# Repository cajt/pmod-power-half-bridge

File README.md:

# pmod-power-half-bridge
This is a power electronics building block for use with an FPGA board that supports PMOD Interfaces. It contains a GAN based half-bridge, an optional LC low-pass output filter, and two ADCs for current and voltage feedback.

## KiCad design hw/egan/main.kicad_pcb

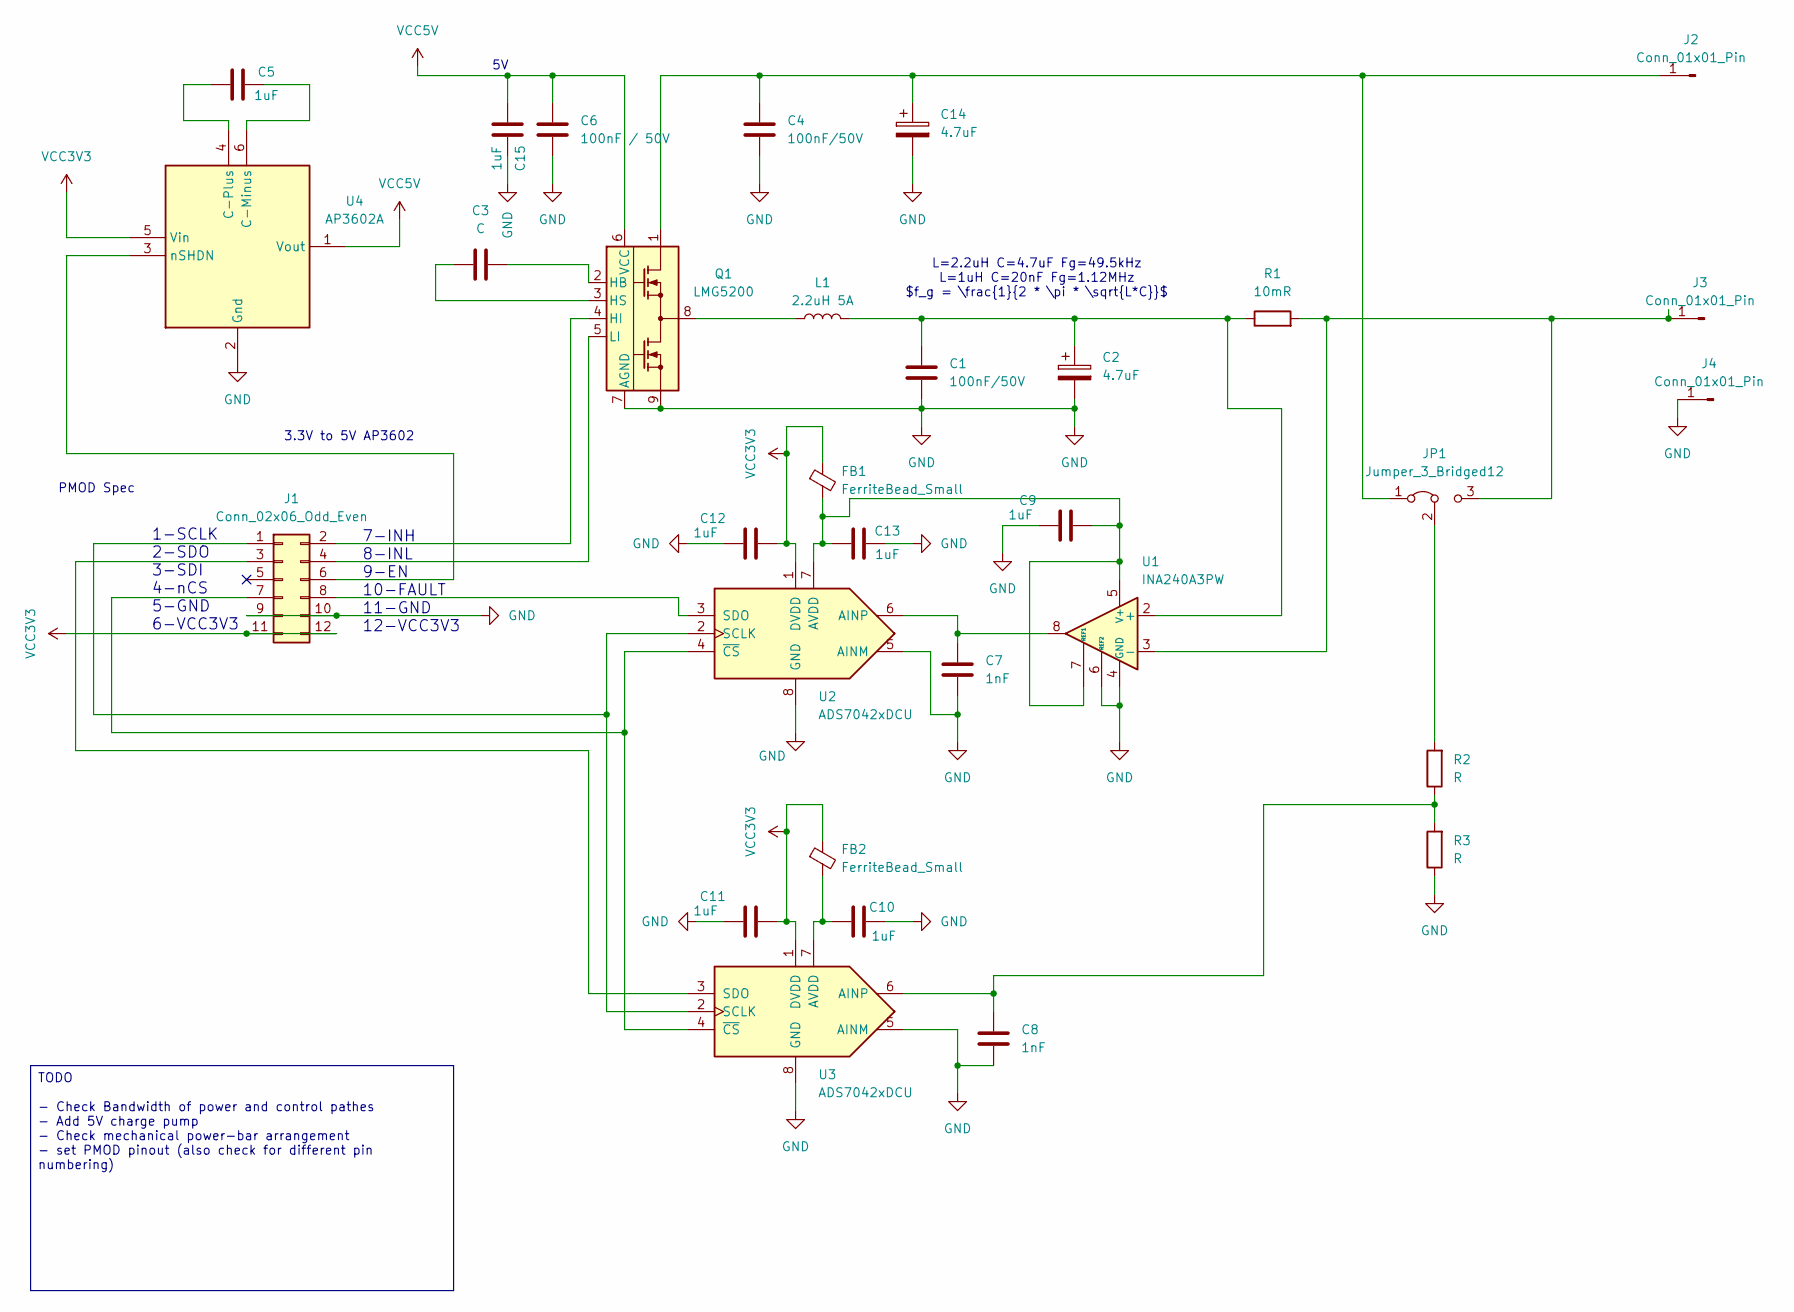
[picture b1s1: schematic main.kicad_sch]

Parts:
C1, C4: 100nF/50V; C_0603_1608Metric_Pad1.08x0.95mm_HandSolder
C2, C14: 4.7uF; CP_EIA-7132-28_AVX-C
C3: C; C_0603_1608Metric_Pad1.08x0.95mm_HandSolder
C5, C9, C10, C11, C12, C13, C15: 1uF; C_0603_1608Metric
C6: 100nF / 50V; C_0603_1608Metric_Pad1.08x0.95mm_HandSolder
C7, C8: 1nF; C_0603_1608Metric_Pad1.08x0.95mm_HandSolder
FB1, FB2: FerriteBead_Small; L_Coilcraft_0604HQ_1610Metric
J1: Conn_02x06_Odd_Even; PinHeader_2x06_P2.54mm_Horizontal
J2, J3, J4: Conn_01x01_Pin; MountingHole_3.2mm_M3_Pad_Via
JP1: Jumper_3_Bridged12; SolderJumper-3_P1.3mm_Open_Pad1.0x1.5mm
L1: 2.2uH 5A; L_7.3x7.3_H4.5; mfg# würth 744777002
Q1: LMG5200; Texas_MOF0009A
R1: 10mR; R_2512_6332Metric
R2, R3: R; R_0603_1608Metric_Pad0.98x0.95mm_HandSolder
U1: INA240A3PW; TSSOP-8_4.4x3mm_P0.65mm
U2, U3: ADS7042xDCU; VSSOP-8_2.3x2mm_P0.5mm
U4: AP3602A; TSOT-23-6

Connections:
GND: C1.2, C2.2, C4.2, C6.2, C7.2, C8.2, C9.1, C10.2, C11.1, C12.1, C13.2, C14.2, C15.2, J1.9, J1.10, J4.1, Q1.7 (AGND), Q1.9, R3.1, U1.1 (GND), U1.4 (GND), U1.6 (REF2), U2.5 (AINM), U2.8 (GND), U3.5 (AINM), U3.8 (GND), U4.2 (Gnd)
unnamed: J1.1, U2.2 (SCLK), U3.2 (SCLK)
unnamed: J1.2, Q1.4 (HI)
unnamed: J1.3, U3.3 (SDO)
unnamed: J1.4, Q1.5 (LI)
unnamed: J1.6, U4.3 (nSHDN)
unnamed: J1.7, U2.4 (~CS), U3.4 (~CS)
unnamed: J1.8, U2.3 (SDO)
unnamed: C4.1, C14.1, J2.1, JP1.1 (A), Q1.1
unnamed: J3.1, JP1.3 (B), R1.2, U1.3 (-)
unnamed: JP1.2 (C), R2.2
unnamed: L1.1, Q1.8
unnamed: C3.2, Q1.2 (HB)
unnamed: C3.1, Q1.3 (HS)
unnamed: C1.1, C2.1, L1.2, R1.1, U1.2 (+)
unnamed: C9.2, C13.1, FB1.2, U1.5 (V+), U1.7 (REF1), U2.7 (AVDD)
unnamed: C7.1, U1.8, U2.6 (AINP)
unnamed: C8.1, R2.1, R3.2, U3.6 (AINP)
unnamed: C10.1, FB2.2, U3.7 (AVDD)
unnamed: C5.2, U4.6 (C-Minus)
unnamed: C5.1, U4.4 (C-Plus)
VCC3V3: C11.2, C12.2, FB1.1, FB2.1, J1.11, J1.12, U2.1 (DVDD), U3.1 (DVDD), U4.5 (Vin)
VCC5V: C6.1, C15.1, Q1.6 (VCC), U4.1 (Vout)

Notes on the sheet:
1-SCLK 2-SDO 3-SDI 4-nCS 5-GND 6-VCC3V3
3.3V to 5V AP3602
L=2.2uH C=4.7uF Fg=49.5kHz L=1uH C=20nF Fg=1.12MHz $f_g = \frac{1}{2 * \pi * \sqrt{L*C}}$
PMOD Spec
7-INH 8-INL 9-EN 10-FAULT 11-GND 12-VCC3V3
TODO - Check Bandwidth of power and control pathes - Add 5V charge pump - Check mechanical power-bar arrangement - set PMOD pinout (also check for different pin numbering)

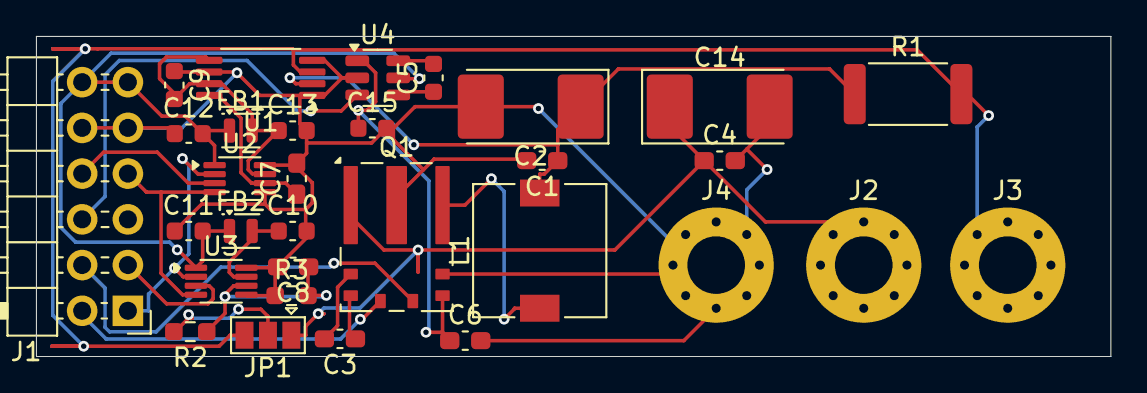
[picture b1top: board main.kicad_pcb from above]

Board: 2 copper layers, 59.7 x 17.8 mm, 31 parts (0 on the bottom side), 23 nets.

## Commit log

2025-09-22 drop some adapted design
2025-09-28 added PDF output for the reader's enjoyment
2025-10-06 add PMOD pinout. mostly inspired by runger's table.
2025-10-06 add the missing PDF udpate
2025-10-06 Add 5V charge-pump
